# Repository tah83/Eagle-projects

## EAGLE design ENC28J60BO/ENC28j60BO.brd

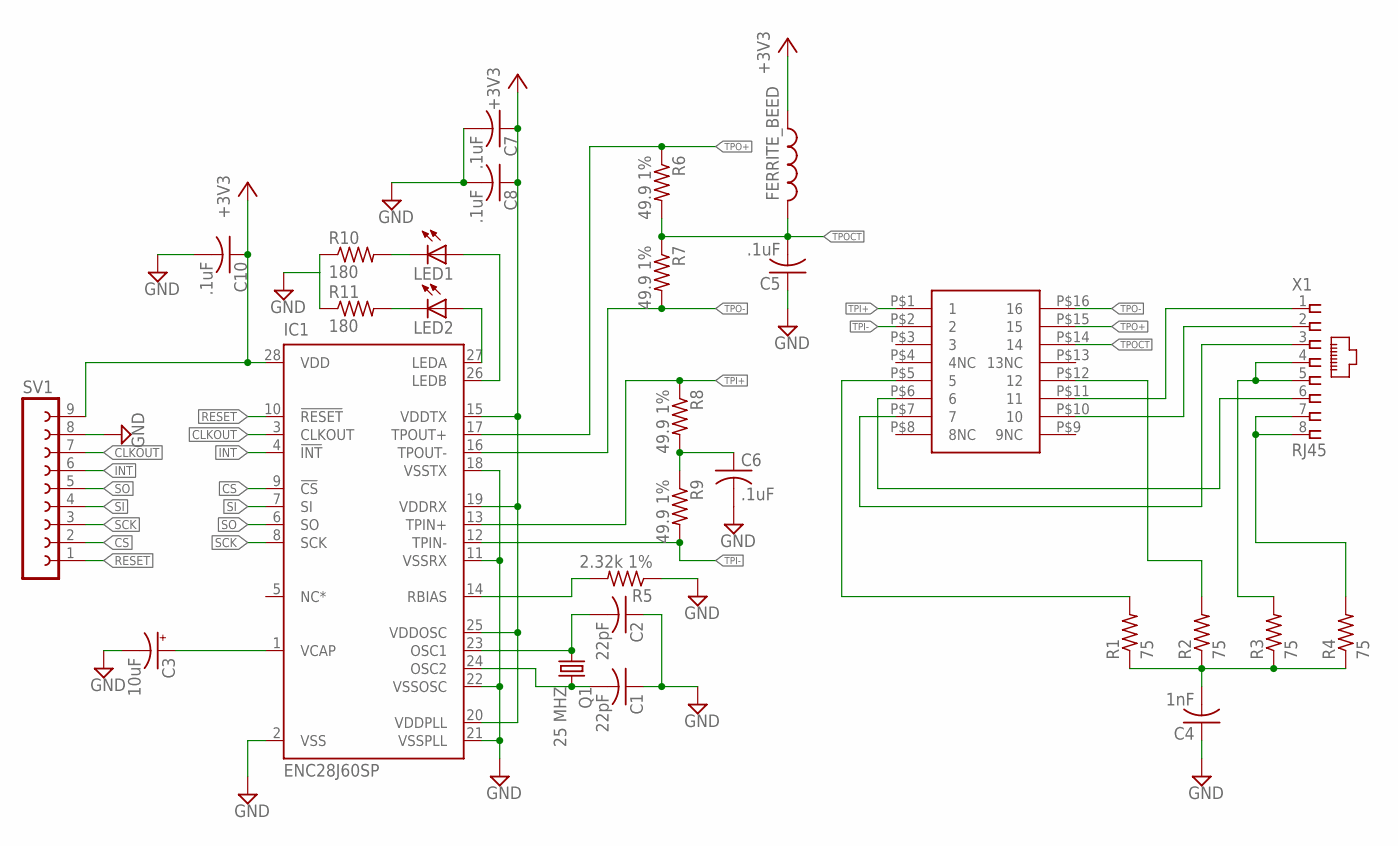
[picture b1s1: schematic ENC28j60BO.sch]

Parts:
C1, C2: 22pF; C025-024X044
C3: 10uF; E2,5-6E
C4: 1nF; C050-025X075
C5, C6, C7, C8, C10: .1uF; C050-024X044
FERRITE_BEED: L-US0204/7; 0204/7
IC1: ENC28J60SP; DIL28-3
LED1, LED2: LED3MM
Q1: 25 MHZ; HC49U-V
R1, R2, R3, R4: 75; 0204/7
R5: 2.32k 1%; 0204/7
R6, R7, R8, R9: 49.9 1%; 0204/7
R10, R11: 180; 0204/7
SV1: FE09-1; FE09
U$1: S558-5999-46-F; DIP16SMD
X1: RJ45

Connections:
+3V3: C7.1, C8.1, C10.1, FERRITE_BEED.1, IC1.15 (VDDTX), IC1.19 (VDDRX), IC1.20 (VDDPLL), IC1.25 (VDDOSC), IC1.28 (VDD), SV1.9
CLKOUT: IC1.3 (CLKOUT), SV1.7
CS: IC1.9 (!CS), SV1.2
GND: C1.1, C2.1, C3.-, C4.1, C5.1, C6.2, C7.2, C8.2, C10.2, IC1.2 (VSS), IC1.11 (VSSRX), IC1.18 (VSSTX), IC1.21 (VSSPLL), IC1.22 (VSSOSC), R5.1, R10.1, R11.1, SV1.8
INT: IC1.4 (!INT), SV1.6
unnamed: C2.2, IC1.23 (OSC1), Q1.1
unnamed: C1.2, IC1.24 (OSC2), Q1.2
unnamed: C3.+, IC1.1 (VCAP)
unnamed: IC1.27 (LEDA), LED2.A
unnamed: U$1.P$10 (10), X1.2
unnamed: U$1.P$7 (7), X1.3
unnamed: U$1.P$6 (6), X1.6
unnamed: U$1.P$11 (11), X1.1
unnamed: R3.2, X1.4, X1.5
unnamed: R4.2, X1.7, X1.8
unnamed: C4.2, R1.1, R2.1, R3.1, R4.1
unnamed: IC1.26 (LEDB), LED1.A
unnamed: R2.2, U$1.P$12 (12)
unnamed: R1.2, U$1.P$5 (5)
unnamed: IC1.14 (RBIAS), R5.2
unnamed: C6.1, R8.2, R9.1
unnamed: LED1.K (C), R10.2
unnamed: LED2.K (C), R11.2
RESET: IC1.10 (!RESET), SV1.1
SCK: IC1.8 (SCK), SV1.3
SI: IC1.7 (SI), SV1.4
SO: IC1.6 (SO), SV1.5
TPI+: IC1.13 (TPIN+), R8.1, U$1.P$1 (1)
TPI-: IC1.12 (TPIN-), R9.2, U$1.P$2 (2)
TPO+: IC1.17 (TPOUT+), R6.1, U$1.P$15 (15)
TPO-: IC1.16 (TPOUT-), R7.2, U$1.P$16 (16)
TPOCT: C5.2, FERRITE_BEED.2, R6.2, R7.1, U$1.P$14 (14)

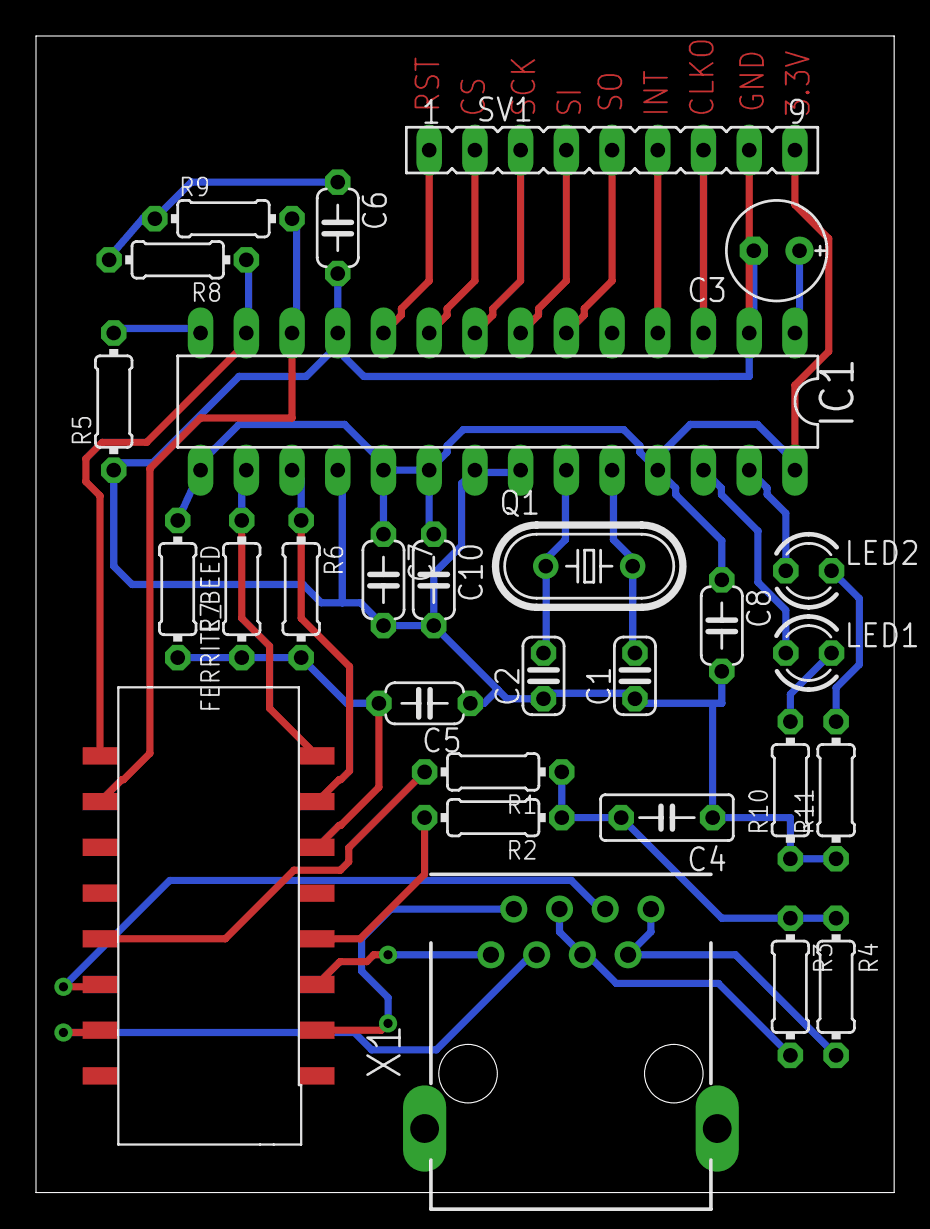
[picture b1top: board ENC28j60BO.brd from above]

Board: 2 copper layers, 47.7 x 64.3 mm, 28 parts (0 on the bottom side), 32 nets.

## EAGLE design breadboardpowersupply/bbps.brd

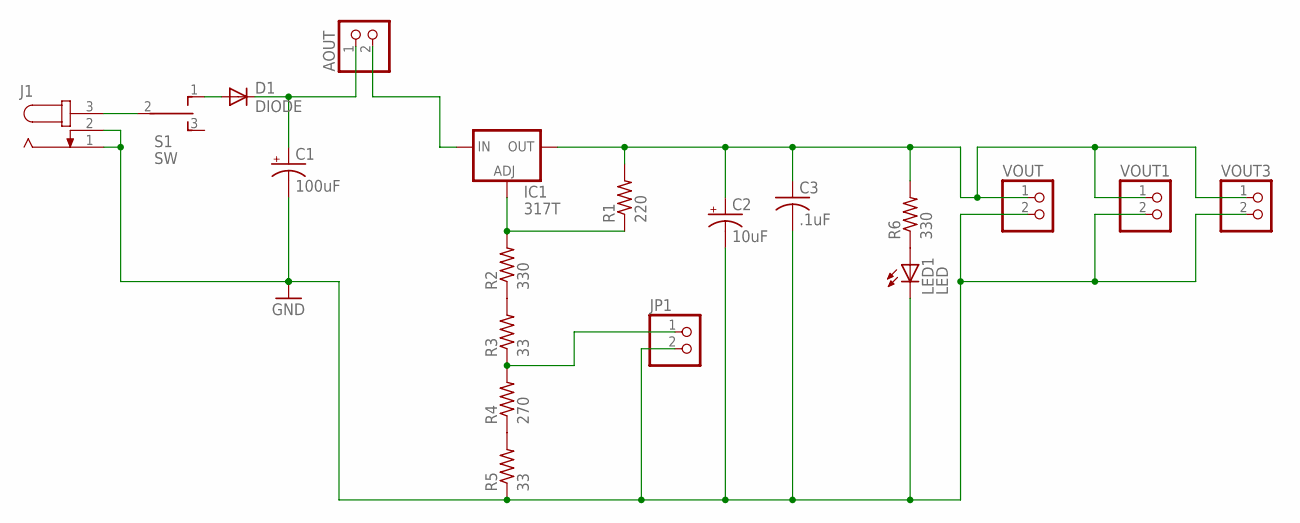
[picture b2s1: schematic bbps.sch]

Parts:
AOUT: PINHD-1X2; 1X02
C1: 100uF; CPOL_5MM
C2: 10uF; CPOL_5MM
C3: .1uF; C050-024X044
D1: DIODE; D40_10MM
IC1: 317T
J1: JACK-PLUG0; SPC4077
JP1: PINHD-1X2; 1X02
LED1: LED; LED_2.54MM
R1: 220; R207_7.6MM
R2, R6: 330; R207_7.6MM
R3, R5: 33; R207_7.6MM
R4: 270; R207_7.6MM
S1: SW; SWITCH
VOUT, VOUT1, VOUT3: PINHD-1X2; 1X02

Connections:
GND: C1.-, C2.-, C3.2, J1.1, J1.2, JP1.2, LED1.K (C), R5.1, VOUT.2, VOUT1.2, VOUT3.2
unnamed: J1.3, S1.2
unnamed: D1.A, S1.1
unnamed: AOUT.1, C1.+, D1.C
unnamed: C2.+, C3.1, IC1.2 (OUT), R1.2, R6.2, VOUT.1, VOUT1.1, VOUT3.1
unnamed: LED1.A, R6.1
unnamed: R4.1, R5.2
unnamed: R2.1, R3.2
unnamed: IC1.1 (ADJ), R1.1, R2.2
unnamed: JP1.1, R3.1, R4.2
unnamed: AOUT.2, IC1.3 (IN)

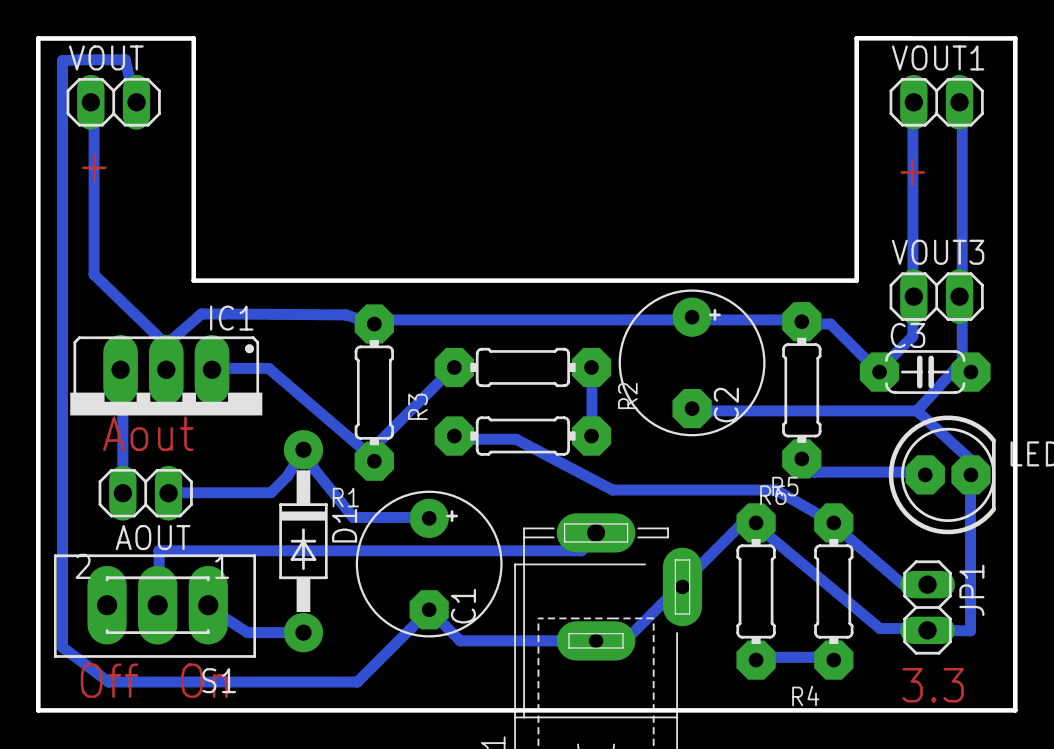
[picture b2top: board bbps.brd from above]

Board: 2 copper layers, 54.3 x 37.3 mm, 19 parts (0 on the bottom side), 11 nets.

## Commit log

2017-04-12 enc28j60
